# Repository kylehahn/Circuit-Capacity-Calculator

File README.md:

# Circuit Capacity Calculator

Native Qt 6 + C++20 desktop calculator and 3D editor for capacitance of
layered PCB topologies, solved via BEM. The original browser prototype
(`sensor3d_editor.html`) is kept separately as a behavioural reference.

## Quick start (any platform)

```
git clone <repo-url> circuit-capacity-calculator
cd circuit-capacity-calculator
# 1. Bootstrap vcpkg (one-time per machine, idempotent):
tools/bootstrap.sh         # macOS / Linux
tools\bootstrap.ps1        # Windows (PowerShell)

# 2. Configure + build:
cmake --preset linux-release        # macos-release / windows-release
cmake --build --preset linux-release -j
ctest --preset linux-release

# 3. Run:
./build/linux-release/circuit_capacity_calculator
```

> First configure compiles Qt from source via vcpkg — **30–60 minutes**. Every
> subsequent configure on the same machine is seconds, and CI/cache covers
> other machines.

## Prerequisites

| Platform | Compiler | Other |
|----------|----------|-------|
| Windows  | Visual Studio 2022 (MSVC + "C++ CMake tools for Windows") | Git, PowerShell 7 |
| macOS    | Xcode 15+ command-line tools                    | Homebrew, `brew install cmake ninja pkg-config` |
| Linux    | GCC 12+ or Clang 15+                            | `sudo apt install build-essential cmake ninja-build git pkg-config libgl1-mesa-dev libxkbcommon-dev libxcb*-dev libxkbcommon-x11-dev` (full list in `.github/workflows/build.yml`) |

CMake **3.25** or newer. Ninja generator (faster than Visual Studio's MSBuild
generator). On Windows, Ninja and MSVC ship inside Visual Studio's
**Developer PowerShell** — the build commands below must be run from that
shell, not regular PowerShell:

> Start menu → search "**Developer PowerShell for VS 2022**" → run from there.
> Or open the project folder in Visual Studio and use its built-in terminal.

## Multi-machine workflow

This project is set up to move cleanly between machines:

- vcpkg is cloned into `external/vcpkg/` and pinned to a baseline. Both are
  managed by `tools/bootstrap.*` and never committed.
- CMake presets reference the bundled vcpkg, so no environment variables are
  needed.
- A pull → configure → build cycle on a new machine is the same three commands
  as above.

### Build cache (recommended)

Install **sccache** so re-builds across machines / sessions are fast:

```
# macOS
brew install sccache
# Windows
scoop install sccache         # or  winget install sccache
# Ubuntu
sudo apt install sccache
```

`CMakePresets.json` already wires `CMAKE_C{,XX}_COMPILER_LAUNCHER=sccache`, so
once it is on `PATH` it is used automatically. To share the cache across
machines, set `SCCACHE_BUCKET=<your-s3-bucket>` (and credentials) before
running configure — sccache will pull pre-built objects on the second
machine.

## Layout

```
circuit-capacity-calculator/
├── CLAUDE.md                project context for the AI dev assistant
├── README.md                this file
├── CMakeLists.txt           top-level build
├── CMakePresets.json        per-platform presets (Win/Mac/Linux × Debug/Release)
├── vcpkg.json               manifest: Qt6, Eigen, tinygltf, nlohmann_json, Catch2
├── .clang-format            C++ formatting (Google base, 110 cols)
├── .editorconfig            editor-agnostic basics
├── .gitignore / .gitattributes
├── src/                     application source
│   ├── CMakeLists.txt
│   └── main.cpp             scaffold entry point — replace with real UI
├── tests/                   Catch2 v3 tests, mirror src/
│   ├── CMakeLists.txt
│   └── test_smoke.cpp
├── tools/                   dev scripts (bootstrap, formatting, …)
│   ├── bootstrap.sh
│   └── bootstrap.ps1
├── .github/workflows/       CI matrix: Windows / macOS / Linux × Release
│   └── build.yml
└── external/                vcpkg lives here after bootstrap (gitignored)
```

## A note on paths with spaces

If your local clone path contains spaces, CMake and vcpkg can occasionally
misbehave. The safe move is to clone this repo into a path **without spaces**,
e.g. `C:\dev\circuit-capacity-calculator` or `~/code/circuit-capacity-calculator`.
The scaffold itself is portable — just `git clone` to the new path on the
new machine.

## License

TBD — add `LICENSE` in the repo root before publishing.

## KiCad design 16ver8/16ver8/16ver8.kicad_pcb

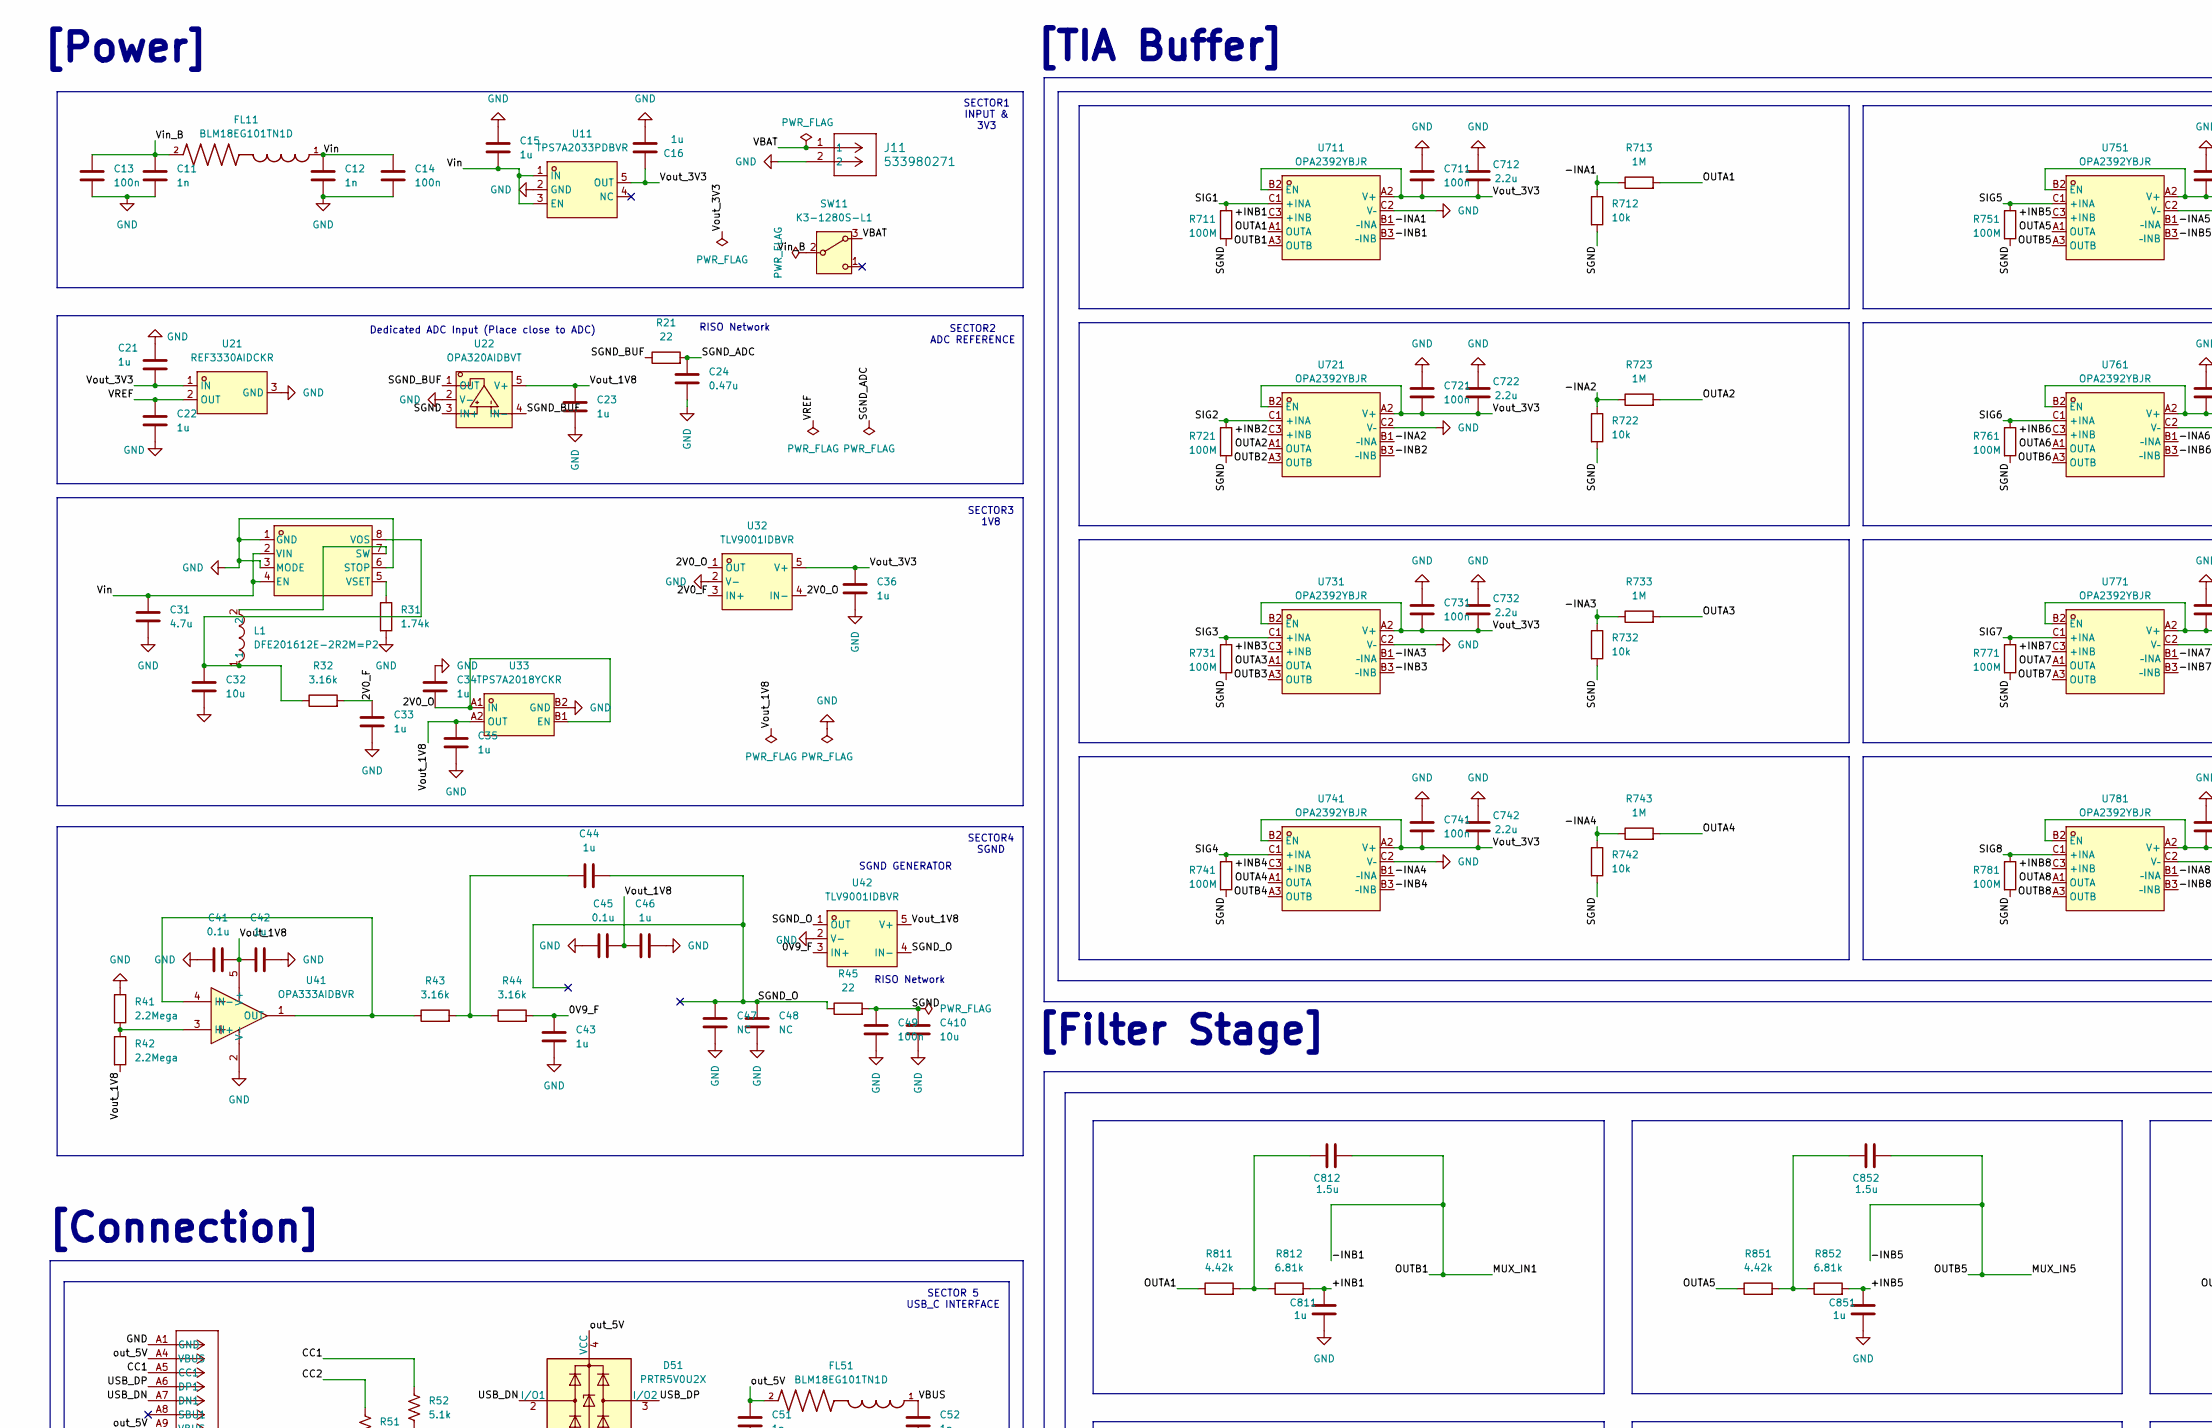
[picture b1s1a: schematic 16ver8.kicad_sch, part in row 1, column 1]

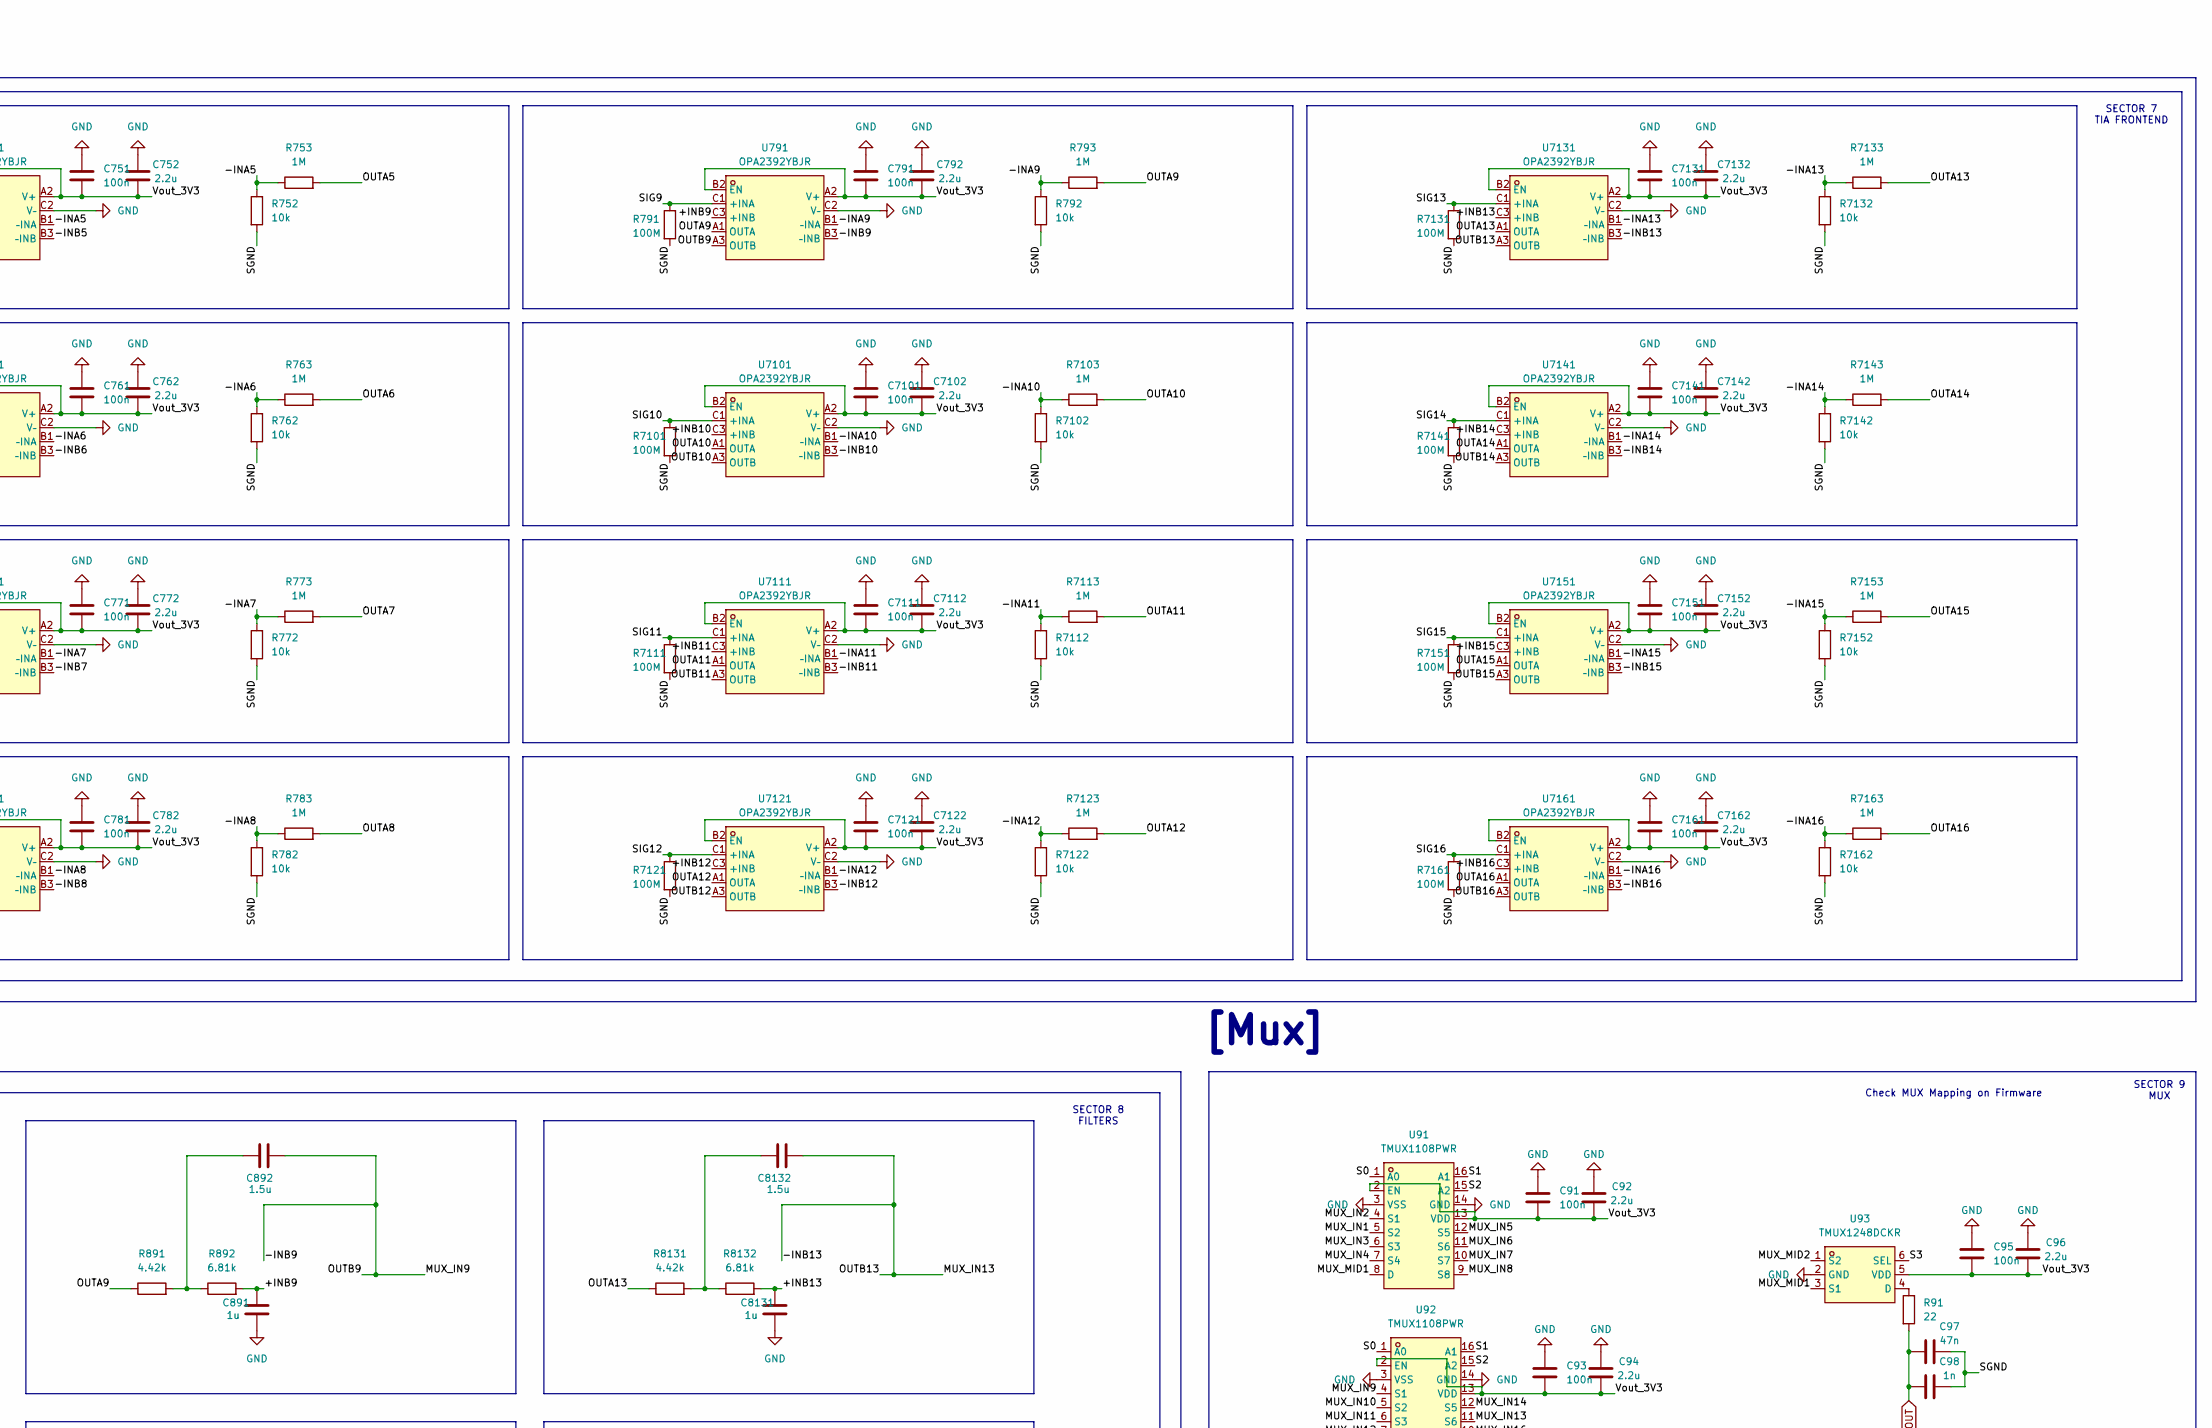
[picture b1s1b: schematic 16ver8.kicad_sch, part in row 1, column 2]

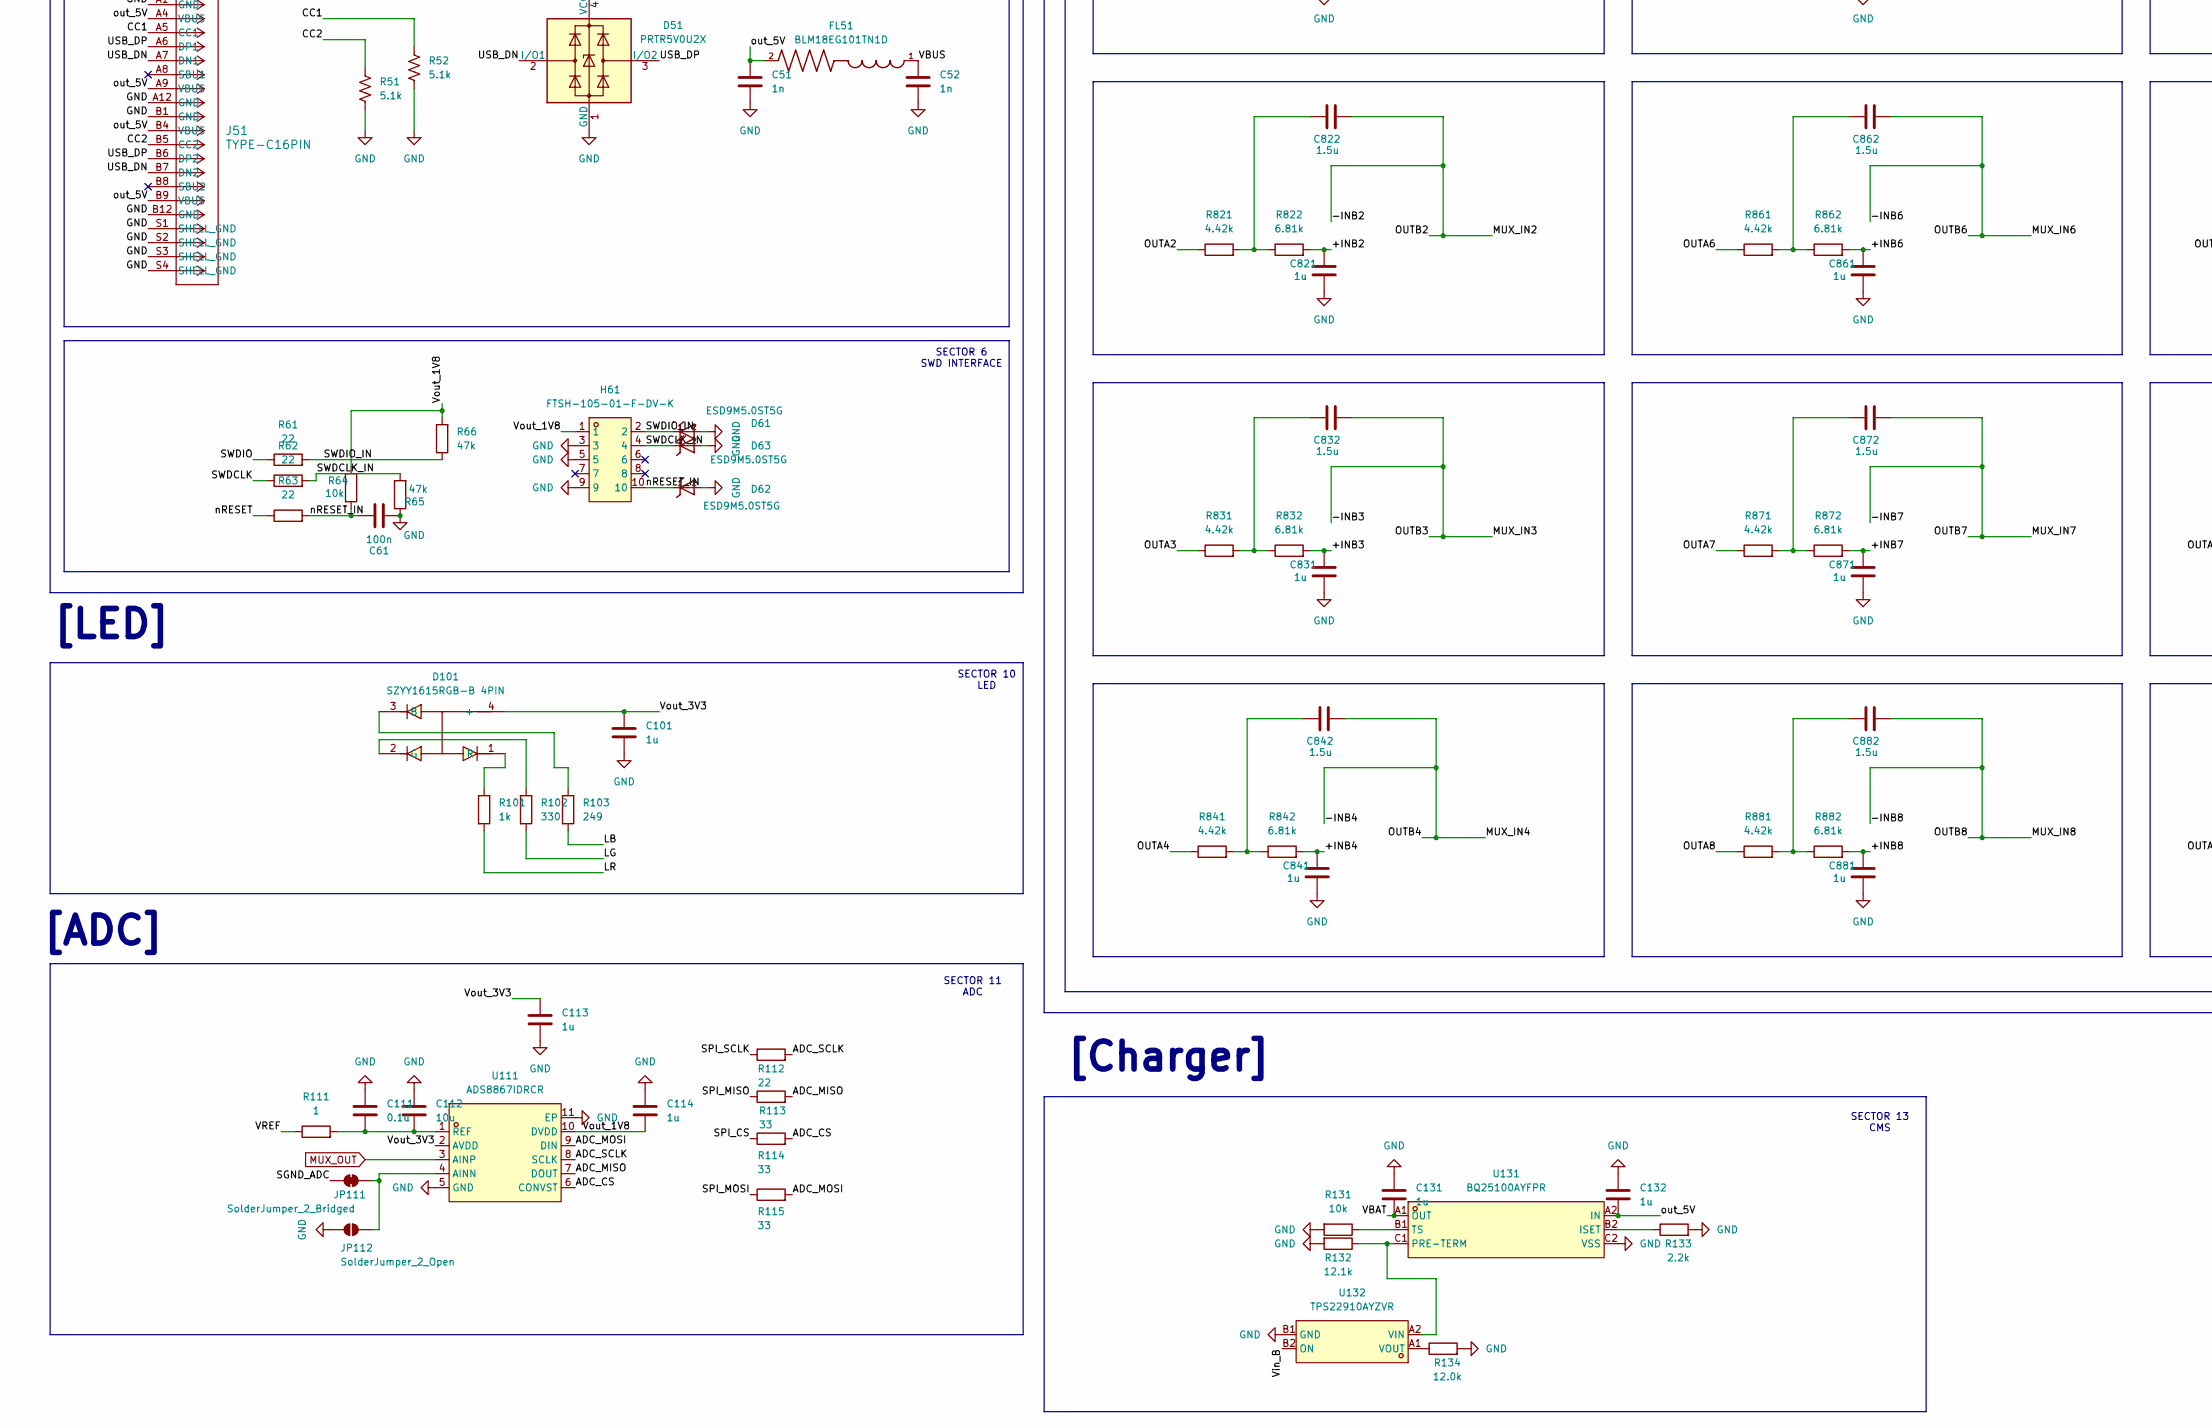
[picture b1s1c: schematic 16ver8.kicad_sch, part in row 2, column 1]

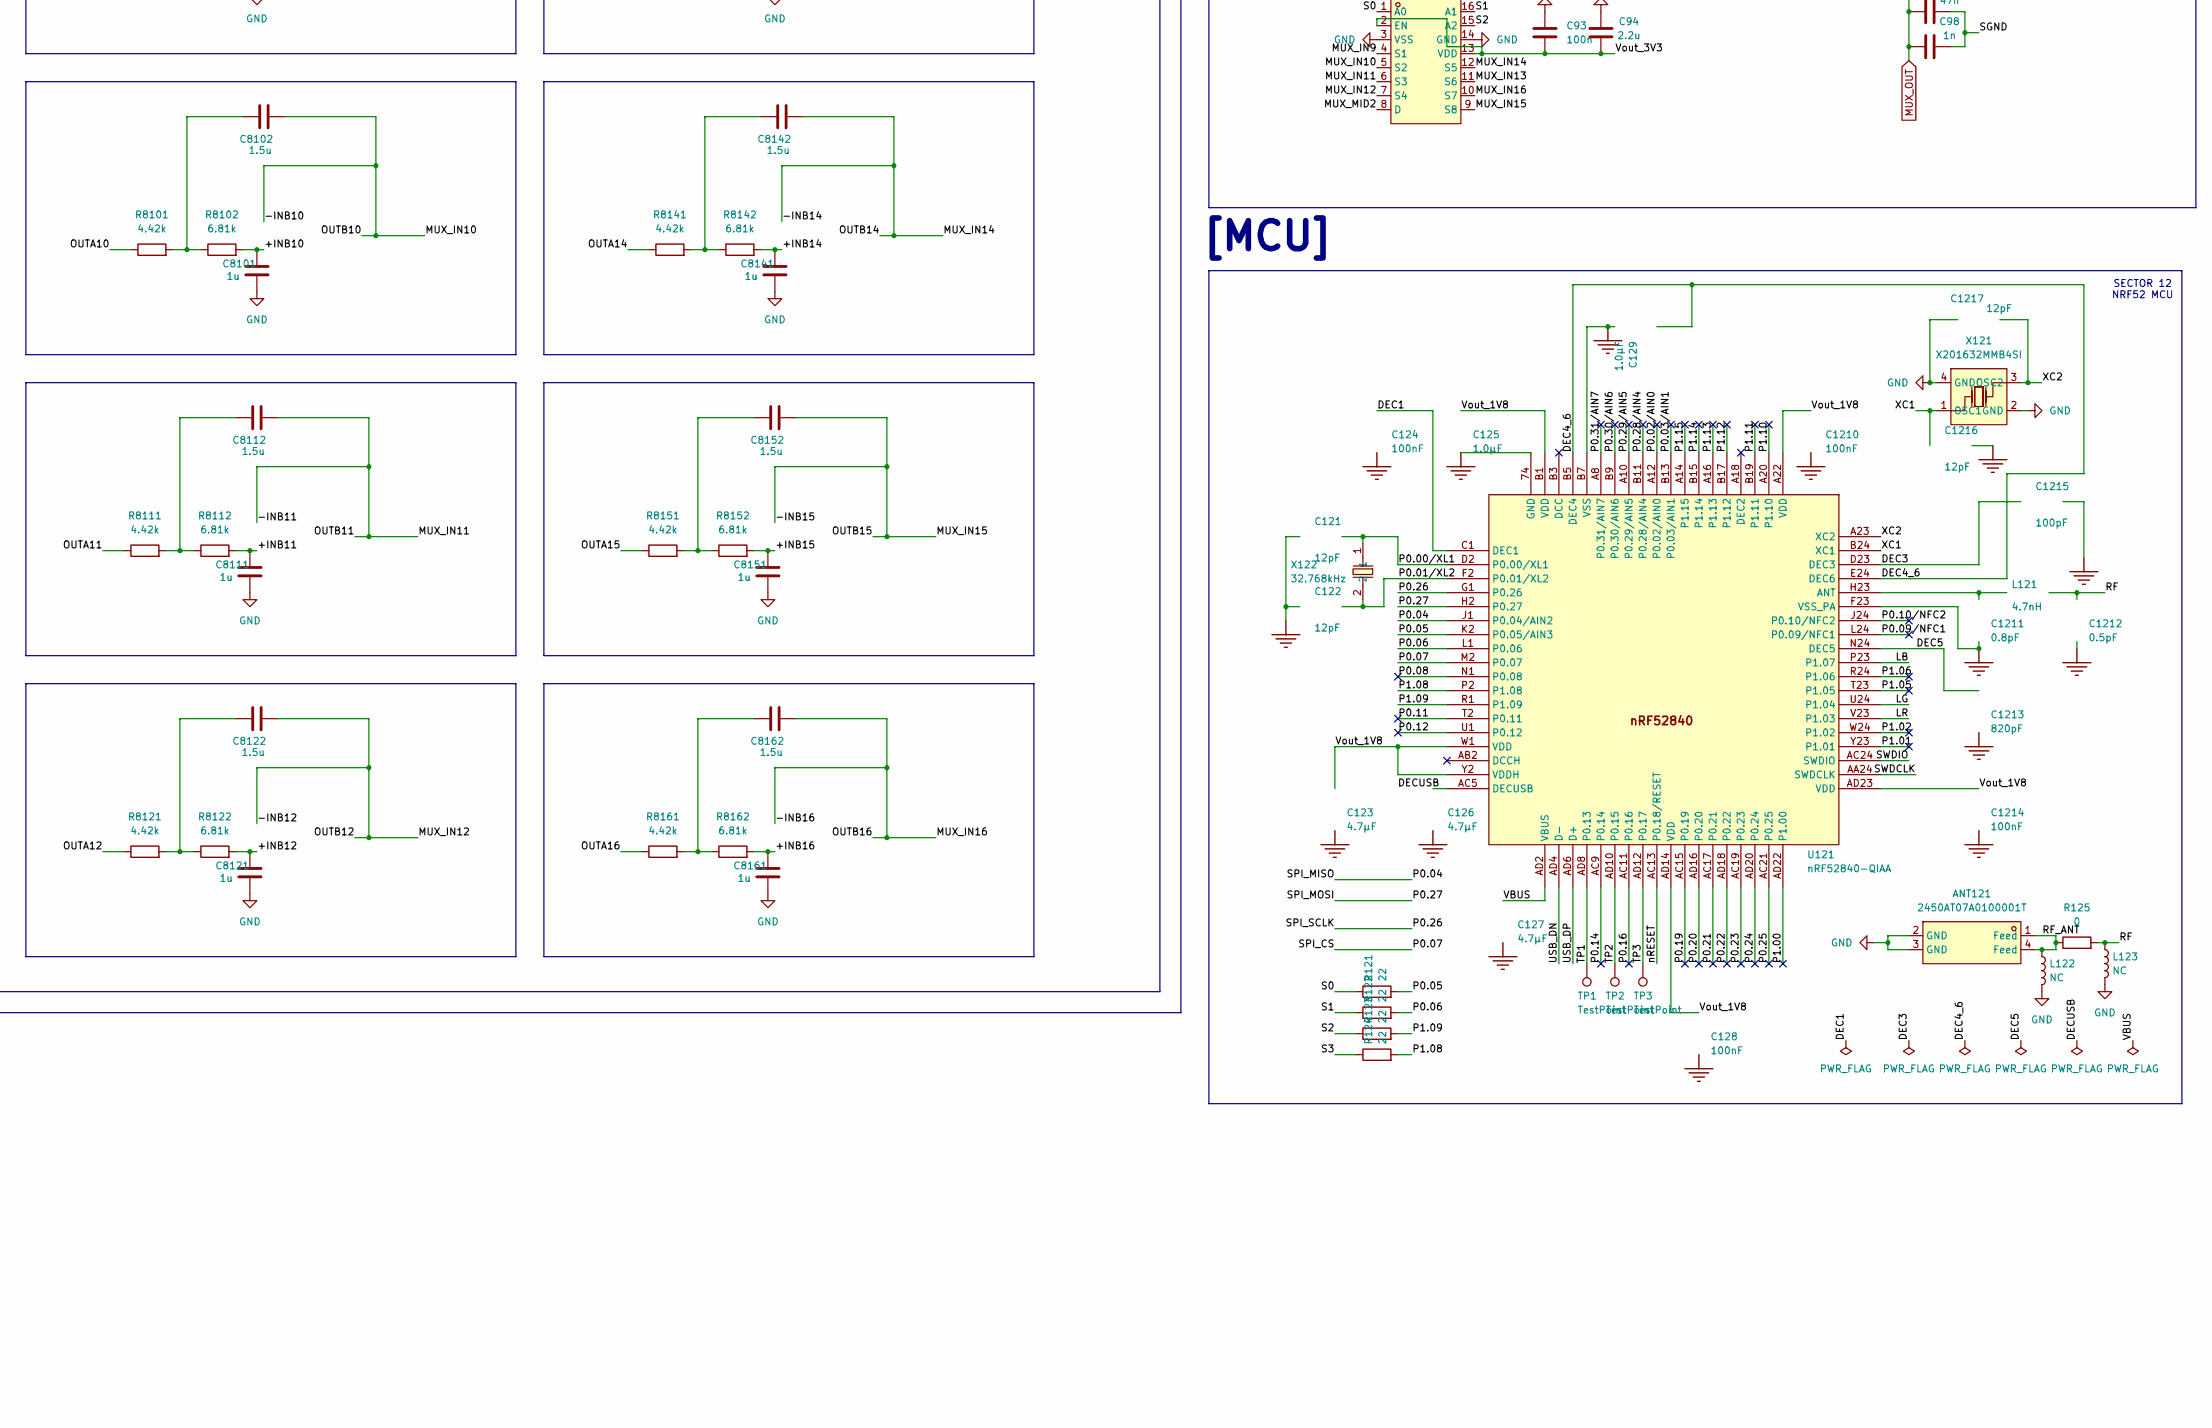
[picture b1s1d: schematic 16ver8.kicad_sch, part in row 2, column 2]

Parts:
ANT121: 2450AT07A0100001T; ANT-SMD_4P-L1.0-W0.5_2450AT07A0100001T; LCSC Part C17531353
C11, C12, C98: 1n; C_0402_1005Metric
C13, C14, C49, C61, C91, C93, C95, C711, C721, C731, C741, C751, C761, C771, C781, C791, C7101, C7111, C7121, C7131, C7141, C7151, C7161: 100n; C_0402_1005Metric
C15, C16, C21, C22, C23, C33, C34, C35, C36, C42, C46, C114, C811, C821, C831, C841, C851, C861, C871, C881, C891, C8101, C8111, C8121, C8131, C8141, C8151, C8161: 1u; C_0603_1608Metric
C24: 0.47u; C_0603_1608Metric
C31: 4.7u; C_0603_1608Metric
C32, C112, C410: 10u; C_0603_1608Metric
C41, C45: 0.1u; C_0402_1005Metric
C43, C44, C101, C113, C131, C132: 1u; C_0402_1005Metric
C47: NC; C_0402_1005Metric
C48: NC; C_0603_1608Metric
C51, C52: 1n; C_0603_1608Metric
C92, C94, C96, C712, C722, C732, C742, C752, C762, C772, C782, C792, C7102, C7112, C7122, C7132, C7142, C7152, C7162: 2.2u; C_0603_1608Metric
C97: 47n; C_0402_1005Metric
C111: 0.1u; C_0603_1608Metric
C121, C122, C1216, C1217: 12pF; CAPC1005X04L; PART NUMBER C0402-12p
C123, C126: 4.7µF; CAPC1608X06L; PART NUMBER C0603-4µ7-6.3V-X7R
C124, C128, C1210, C1214: 100nF; CAPC1005X04L; PART NUMBER C0402-100n
C125, C129: 1.0µF; CAPC1608X06L; PART NUMBER C0603-1µ0
C127: 4.7µF; CAPC1608X06L; PART NUMBER C0603-4µ7-10V-X7S
C812, C822, C832, C842, C852, C862, C872, C882, C892, C8102, C8112, C8122, C8132, C8142, C8152, C8162: 1.5u; C_0603_1608Metric
C1211: 0.8pF; CAPC1005X04L; PART NUMBER C0402-0.8p
C1212: 0.5pF; CAPC1005X04L; PART NUMBER C0402-0.5p
C1213: 820pF; CAPC1005X04L; PART NUMBER C0402-820p
C1215: 100pF; CAPC1005X04L; PART NUMBER C0402-100p
D51: PRTR5V0U2X; SOT-143
D61, D62, D63: ESD9M5.0ST5G; SODFL1060X40N
D101: SZYY1615RGB-B 4PIN; LED-SMD_4P-L1.6-W1.5-TR-1; LCSC Part C3029071
FL11, FL51: BLM18EG101TN1D; BEADC1608X65N
H61: FTSH-105-01-F-DV-K; HDR-SMD_FTSH-105-01-F-DV-K; LCSC Part C5382952
J11: 533980271; CONN02_533980271_MOL
J51: TYPE-C16PIN; TYPE-C-SMD_SBC-160S1A-20-S412
JP111: SolderJumper_2_Bridged; SolderJumper-2_P1.3mm_Bridged2Bar_Pad1.0x1.5mm
JP112: SolderJumper_2_Open; SolderJumper-2_P1.3mm_Open_Pad1.0x1.5mm
L1: DFE201612E-2R2M=P2; L0806; LCSC Part C337893
L121: 4.7nH; INDC1005X04L; PART NUMBER L0402-4n7
L122, L123: NC; L_0402_1005Metric
R21, R45, R61, R62, R63, R91, R112, R121, R122, R123, R124: 22; R_0402_1005Metric
R31: 1.74k; R_0402_1005Metric
R32, R43, R44: 3.16k; R_0402_1005Metric
R41, R42: 2.2Mega; R_0402_1005Metric
R51, R52: 5.1k; R_0402_1005Metric
R64, R131, R712, R722, R732, R742, R752, R762, R772, R782, R792, R7102, R7112, R7122, R7132, R7142, R7152, R7162: 10k; R_0402_1005Metric
R65, R66: 47k; R_0402_1005Metric
R101: 1k; R_0402_1005Metric
R102: 330; R_0402_1005Metric
R103: 249; R_0402_1005Metric
R111: 1; R_0402_1005Metric
R113, R114, R115: 33; R_0402_1005Metric
R125: 0; R_0402_1005Metric
R132: 12.1k; R_0402_1005Metric
R133: 2.2k; R_0402_1005Metric
R134: 12.0k; R_0402_1005Metric
R711, R721, R731, R741, R751, R761, R771, R781, R791, R7101, R7111, R7121, R7131, R7141, R7151, R7161: 100M; R_0805_2012Metric
R713, R723, R733, R743, R753, R763, R773, R783, R793, R7103, R7113, R7123, R7133, R7143, R7153, R7163: 1M; R_0603_1608Metric
R811, R821, R831, R841, R851, R861, R871, R881, R891, R8101, R8111, R8121, R8131, R8141, R8151, R8161: 4.42k; R_0402_1005Metric
R812, R822, R832, R842, R852, R862, R872, R882, R892, R8102, R8112, R8122, R8132, R8142, R8152, R8162: 6.81k; R_0402_1005Metric
SW11: K3-1280S-L1; SW_Nidec_CAS-120A1
TP1, TP2, TP3: TestPoint; TestPoint_Pad_1.0x1.0mm
U11: TPS7A2033PDBVR; SOT-23-5_L2.9-W1.6-P0.95-LS2.8-BR; LCSC Part C2862740
U21: REF3330AIDCKR; SC-70-3_L2.0-W1.3-P0.65-LS2.1-BL; LCSC Part C2157700
U22: OPA320AIDBVT; SOT-23-5_L2.9-W1.6-P0.95-LS2.8-BL; LCSC Part C206063
U31: TPS62840DLCR; VSON-8_L2.0-W1.5-P0.50-BL
U32, U42: TLV9001IDBVR; SOT-23-5_L3.0-W1.7-P0.95-LS2.8-BR; LCSC Part C398363
U33: TPS7A2018YCKR; BGA-4_L0.6-W0.6-P0.35-R2-C2-TL_TPS7A2012PYCJR; LCSC Part C42038768
U41: OPA333AIDBVR; SOT-23-5_L3.0-W1.7-P0.95-LS2.8-BR; LCSC Part C30878
U91, U92: TMUX1108PWR; TSSOP-16_L5.0-W4.4-P0.65-LS6.4-BL; LCSC Part C1021800
U93: TMUX1248DCKR; SC-70-6_L2.0-W1.3-P0.65-LS2.2-BL; LCSC Part C3656915
U111: ADS8867IDRCR; WSON-10_L3.0-W3.0-P0.50-BL-EP; LCSC Part C545498
U121: nRF52840-QIAA; AQFN-73_L7.0-W7.0-P0.50-BL-EP4.8; PART NUMBER nRF52840-QIAA
U131: BQ25100AYFPR; DSBGA-6_L0.9-W1.6-R2-C3-P0.40-BL; LCSC Part C2871910
U132: TPS22910AYZVR; DSBGA-4_L0.9-W0.9-R2-C2-P0.50-BL; LCSC Part C205966
U711, U721, U731, U741, U751, U761, U771, U781, U791, U7101, U7111, U7121, U7131, U7141, U7151, U7161: OPA2392YBJR; DSBGA-9_L1.2-W1.2-R3-C3-P0.40-BL; LCSC Part C5946032
X121: X201632MMB4SI; CRYSTAL-SMD_4P-L2.0-W1.6-BL; LCSC Part C383840
X122: 32.768kHz; CRYSTAL-SMD_L2.0-W1.2; LCSC Part C32346

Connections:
/0V9_F: C43.1, R44.2, U42.3 (IN+)
/2V0_F: C33.1, R32.2, U32.3 (IN+)
/2V0_O: C34.2, U32.1 (OUT), U32.4 (IN-), U33.A1 (IN), U33.B1 (EN)
/+INB1: C811.1, R812.2, U711.C3 (+INB)
/+INB2: C821.1, R822.2, U721.C3 (+INB)
/+INB3: C831.1, R832.2, U731.C3 (+INB)
/+INB4: C841.1, R842.2, U741.C3 (+INB)
/+INB5: C851.1, R852.2, U751.C3 (+INB)
/+INB6: C861.1, R862.2, U761.C3 (+INB)
/+INB7: C871.1, R872.2, U771.C3 (+INB)
/+INB8: C881.1, R882.2, U781.C3 (+INB)
/+INB9: C891.1, R892.2, U791.C3 (+INB)
/+INB10: C8101.1, R8102.2, U7101.C3 (+INB)
/+INB11: C8111.1, R8112.2, U7111.C3 (+INB)
/+INB12: C8121.1, R8122.2, U7121.C3 (+INB)
/+INB13: C8131.1, R8132.2, U7131.C3 (+INB)
/+INB14: C8141.1, R8142.2, U7141.C3 (+INB)
/+INB15: C8151.1, R8152.2, U7151.C3 (+INB)
/+INB16: C8161.1, R8162.2, U7161.C3 (+INB)
/-INA1: R712.1, R713.1, U711.B1 (–INA)
/-INA2: R722.1, R723.1, U721.B1 (–INA)
/-INA3: R732.1, R733.1, U731.B1 (–INA)
/-INA4: R742.1, R743.1, U741.B1 (–INA)
/-INA5: R752.1, R753.1, U751.B1 (–INA)
/-INA6: R762.1, R763.1, U761.B1 (–INA)
/-INA7: R772.1, R773.1, U771.B1 (–INA)
/-INA8: R782.1, R783.1, U781.B1 (–INA)
/-INA9: R792.1, R793.1, U791.B1 (–INA)
/-INA10: R7102.1, R7103.1, U7101.B1 (–INA)
/-INA11: R7112.1, R7113.1, U7111.B1 (–INA)
/-INA12: R7122.1, R7123.1, U7121.B1 (–INA)
/-INA13: R7132.1, R7133.1, U7131.B1 (–INA)
/-INA14: R7142.1, R7143.1, U7141.B1 (–INA)
/-INA15: R7152.1, R7153.1, U7151.B1 (–INA)
/-INA16: R7162.1, R7163.1, U7161.B1 (–INA)
/-INB1: C812.2, U91.5 (S2), U711.A3 (OUTB), U711.B3 (–INB)
/-INB2: C822.2, U91.4 (S1), U721.A3 (OUTB), U721.B3 (–INB)
/-INB3: C832.2, U91.6 (S3), U731.A3 (OUTB), U731.B3 (–INB)
/-INB4: C842.2, U91.7 (S4), U741.A3 (OUTB), U741.B3 (–INB)
/-INB5: C852.2, U91.12 (S5), U751.A3 (OUTB), U751.B3 (–INB)
/-INB6: C862.2, U91.11 (S6), U761.A3 (OUTB), U761.B3 (–INB)
/-INB7: C872.2, U91.10 (S7), U771.A3 (OUTB), U771.B3 (–INB)
/-INB8: C882.2, U91.9 (S8), U781.A3 (OUTB), U781.B3 (–INB)
/-INB9: C892.2, U92.4 (S1), U791.A3 (OUTB), U791.B3 (–INB)
/-INB10: C8102.2, U92.5 (S2), U7101.A3 (OUTB), U7101.B3 (–INB)
/-INB11: C8112.2, U92.6 (S3), U7111.A3 (OUTB), U7111.B3 (–INB)
/-INB12: C8122.2, U92.7 (S4), U7121.A3 (OUTB), U7121.B3 (–INB)
/-INB13: C8132.2, U92.11 (S6), U7131.A3 (OUTB), U7131.B3 (–INB)
/-INB14: C8142.2, U92.12 (S5), U7141.A3 (OUTB), U7141.B3 (–INB)
/-INB15: C8152.2, U92.9 (S8), U7151.A3 (OUTB), U7151.B3 (–INB)
/-INB16: C8162.2, U92.10 (S7), U7161.A3 (OUTB), U7161.B3 (–INB)
/ADC_CS: R114.2, U111.6 (CONVST)
/ADC_MISO: R113.2, U111.7 (DOUT)
/ADC_MOSI: R115.2, U111.9 (DIN)
/ADC_SCLK: R112.2, U111.8 (SCLK)
/CC1: J51.A5 (CC1), R52.1
/CC2: J51.B5 (CC2), R51.1
/DEC1: C124.1, U121.C1 (DEC1)
/DEC3: C1215.1, U121.D23 (DEC3)
/DEC4_6: C129.2, U121.B5 (DEC4), U121.E24 (DEC6)
/DEC5: C1213.1, U121.N24 (DEC5)
/DECUSB: C126.1, U121.AC5 (DECUSB)
/LB: R103.2, U121.P23 (P1.07)
/LG: R102.2, U121.U24 (P1.04)
/LR: R101.2, U121.V23 (P1.03)
/MUX_MID1: U91.8 (D), U93.3 (S1)
/MUX_MID2: U92.8 (D), U93.1 (S2)
/OUTA1: R713.2, R811.1, U711.A1 (OUTA)
/OUTA2: R723.2, R821.1, U721.A1 (OUTA)
/OUTA3: R733.2, R831.1, U731.A1 (OUTA)
/OUTA4: R743.2, R841.1, U741.A1 (OUTA)
/OUTA5: R753.2, R851.1, U751.A1 (OUTA)
/OUTA6: R763.2, R861.1, U761.A1 (OUTA)
/OUTA7: R773.2, R871.1, U771.A1 (OUTA)
/OUTA8: R783.2, R881.1, U781.A1 (OUTA)
/OUTA9: R793.2, R891.1, U791.A1 (OUTA)
/OUTA10: R7103.2, R8101.1, U7101.A1 (OUTA)
/OUTA11: R7113.2, R8111.1, U7111.A1 (OUTA)
/OUTA12: R7123.2, R8121.1, U7121.A1 (OUTA)
/OUTA13: R7133.2, R8131.1, U7131.A1 (OUTA)
/OUTA14: R7143.2, R8141.1, U7141.A1 (OUTA)
/OUTA15: R7153.2, R8151.1, U7151.A1 (OUTA)
/OUTA16: R7163.2, R8161.1, U7161.A1 (OUTA)
/P0.00/XL1: C121.1, U121.D2 (P0.00/XL1), X122.1
/P0.01/XL2: C122.1, U121.F2 (P0.01/XL2), X122.2
/P0.02/AIN0: U121.A12 (P0.02/AIN0)
/P0.03/AIN1: U121.B13 (P0.03/AIN1)
/P0.04: R113.1, U121.J1 (P0.04/AIN2)
/P0.05: R121.2, U121.K2 (P0.05/AIN3)
/P0.06: R122.2, U121.L1 (P0.06)
/P0.07: R114.1, U121.M2 (P0.07)
/P0.08: U121.N1 (P0.08)
/P0.09/NFC1: U121.L24 (P0.09/NFC1)
/P0.10/NFC2: U121.J24 (P0.10/NFC2)
/P0.11: U121.T2 (P0.11)
/P0.12: U121.U1 (P0.12)
/P0.14: U121.AC9 (P0.14)
/P0.16: U121.AC11 (P0.16)
/P0.19: U121.AC15 (P0.19)
/P0.20: U121.AD16 (P0.20)
/P0.21: U121.AC17 (P0.21)
/P0.22: U121.AD18 (P0.22)
/P0.23: U121.AC19 (P0.23)
/P0.24: U121.AD20 (P0.24)
/P0.25: U121.AC21 (P0.25)
/P0.26: R112.1, U121.G1 (P0.26)
/P0.27: R115.1, U121.H2 (P0.27)
/P0.28/AIN4: U121.B11 (P0.28/AIN4)
/P0.29/AIN5: U121.A10 (P0.29/AIN5)
/P0.30/AIN6: U121.B9 (P0.30/AIN6)
/P0.31/AIN7: U121.A8 (P0.31/AIN7)
/P1.00: U121.AD22 (P1.00)
/P1.01: U121.Y23 (P1.01)
/P1.02: U121.W24 (P1.02)
/P1.05: U121.T23 (P1.05)
/P1.06: U121.R24 (P1.06)
/P1.08: R124.2, U121.P2 (P1.08)
/P1.09: R123.2, U121.R1 (P1.09)
/P1.10: U121.A20 (P1.10)
/P1.11: U121.B19 (P1.11)
/P1.12: U121.B17 (P1.12)
/P1.13: U121.A16 (P1.13)
/P1.14: U121.B15 (P1.14)
/P1.15: U121.A14 (P1.15)
/RF: C1212.2, L121.2, L123.1, R125.2
/RF_ANT: ANT121.1 (Feed), ANT121.4 (Feed), L122.1, R125.1
/S0: R121.1, U91.1 (A0), U92.1 (A0)
/S1: R122.1, U91.16 (A1), U92.16 (A1)
/S2: R123.1, U91.15 (A2), U92.15 (A2)
/S3: R124.1, U93.6 (SEL)
/SGND: C49.2, C97.2, C98.2, C410.1, R45.2, R711.2, R712.2, R721.2, R722.2, R731.2, R732.2, R741.2, R742.2, R751.2, R752.2, R761.2, R762.2, R771.2, R772.2, R781.2, R782.2, R791.2, R792.2, R7101.2, R7102.2, R7111.2, R7112.2, R7121.2, R7122.2, R7131.2, R7132.2, R7141.2, R7142.2, R7151.2, R7152.2, R7161.2, R7162.2, U22.3 (IN+)
/SGND_ADC: C24.1, JP111.2 (B), R21.2
/SGND_BUF: R21.1, U22.1 (OUT), U22.4 (IN-)
/SGND_O: C44.2, C47.2, C48.1, R45.1, U42.1 (OUT), U42.4 (IN-)
/SIG1: R711.1, U711.C1 (+INA)
/SIG2: R721.1, U721.C1 (+INA)
/SIG3: R731.1, U731.C1 (+INA)
/SIG4: R741.1, U741.C1 (+INA)
/SIG5: R751.1, U751.C1 (+INA)
/SIG6: R761.1, U761.C1 (+INA)
/SIG7: R771.1, U771.C1 (+INA)
/SIG8: R781.1, U781.C1 (+INA)
/SIG9: R791.1, U791.C1 (+INA)
/SIG10: R7101.1, U7101.C1 (+INA)
/SIG11: R7111.1, U7111.C1 (+INA)
/SIG12: R7121.1, U7121.C1 (+INA)
/SIG13: R7131.1, U7131.C1 (+INA)
/SIG14: R7141.1, U7141.C1 (+INA)
/SIG15: R7151.1, U7151.C1 (+INA)
/SIG16: R7161.1, U7161.C1 (+INA)
/SWDCLK: R62.1, U121.AA24 (SWDCLK)
/SWDCLK_IN: D63.1, H61.4, R62.2, R65.2
/SWDIO: R61.1, U121.AC24 (SWDIO)
/SWDIO_IN: D61.1, H61.2, R61.2, R66.1
/TP1: TP1.1, U121.AD8 (P0.13)
/TP2: TP2.1, U121.AD10 (P0.15)
/TP3: TP3.1, U121.AD12 (P0.17)
/USB_DN: D51.2 (I/O1), J51.A7 (DN1), J51.B7 (DN2), U121.AD4 (D-)
/USB_DP: D51.3 (I/O2), J51.A6 (DP1), J51.B6 (DP2), U121.AD6 (D+)
/VBAT: C131.1, J11.1, SW11.3 (A), U131.A1 (OUT)
/VBUS: C52.1, C127.1, FL51.1, U121.AD2 (VBUS)
/VREF: C22.1, R111.1, U21.2 (OUT)
/Vin: C12.1, C14.1, C15.2, C31.1, FL11.1, U11.1 (IN), U11.3 (EN), U31.2 (VIN), U31.4 (EN)
/Vin_B: C11.1, C13.1, FL11.2, SW11.2 (B), U132.B2 (ON)
/Vout_1V8: C23.1, C35.1, C41.2, C42.1, C45.2, C46.1, C114.2, C123.1, C125.1, C128.1, C1210.1, C1214.1, H61.1, R42.2, R64.1, R66.2, U22.5 (V+), U33.A2 (OUT), U41.5 (V+), U42.5 (V+), U111.10 (DVDD), U121.A22 (VDD), U121.AD14 (VDD), U121.AD23 (VDD), U121.B1 (VDD), U121.W1 (VDD), U121.Y2 (VDDH)
/Vout_3V3: C16.1, C21.1, C36.1, C91.1, C92.1, C93.1, C94.1, C95.1, C96.1, C101.1, C113.1, C711.1, C712.1, C721.1, C722.1, C731.1, C732.1, C741.1, C742.1, C751.1, C752.1, C761.1, C762.1, C771.1, C772.1, C781.1, C782.1, C791.1, C792.1, C7101.1, C7102.1, C7111.1, C7112.1, C7121.1, C7122.1, C7131.1, C7132.1, C7141.1, C7142.1, C7151.1, C7152.1, C7161.1, C7162.1, D101.4 (+), U11.5 (OUT), U21.1 (IN), U32.5 (V+), U91.2 (EN), U91.13 (VDD), U92.2 (EN), U92.13 (VDD), U93.5 (VDD), U111.2 (AVDD), U711.A2 (V+), U711.B2 (EN), U721.A2 (V+), U721.B2 (EN), U731.A2 (V+), U731.B2 (EN), U741.A2 (V+), U741.B2 (EN), U751.A2 (V+), U751.B2 (EN), U761.A2 (V+), U761.B2 (EN), U771.A2 (V+), U771.B2 (EN), U781.A2 (V+), U781.B2 (EN), U791.A2 (V+), U791.B2 (EN), U7101.A2 (V+), U7101.B2 (EN), U7111.A2 (V+), U7111.B2 (EN), U7121.A2 (V+), U7121.B2 (EN), U7131.A2 (V+), U7131.B2 (EN), U7141.A2 (V+), U7141.B2 (EN), U7151.A2 (V+), U7151.B2 (EN), U7161.A2 (V+), U7161.B2 (EN)
/XC1: C1216.1, U121.B24 (XC1), X121.1 (OSC1)
/XC2: C1217.1, U121.A23 (XC2), X121.3 (OSC2)
/nRESET: R63.1, U121.AC13 (P0.18/RESET)
/nRESET_IN: C61.2, D62.1, H61.10, R63.2, R64.2
/out_5V: C51.1, C132.1, D51.4 (VCC), FL51.2, J51.A4 (VBUS), J51.A9 (VBUS), J51.B4 (VBUS), J51.B9 (VBUS), U131.A2 (IN)
GND: ANT121.2 (GND), ANT121.3 (GND), C11.2, C12.2, C13.2, C14.2, C15.1, C16.2, C21.2, C22.2, C23.2, C24.2, C31.2, C32.2, C33.2, C34.1, C35.2, C36.2, C41.1, C42.2, C43.2, C45.1, C46.2, C47.1, C48.2, C49.1, C51.2, C52.2, C61.1, C91.2, C92.2, C93.2, C94.2, C95.2, C96.2, C101.2, C111.1, C112.1, C113.2, C114.1, C121.2, C122.2, C123.2, C124.2, C125.2, C126.2, C127.2, C128.2, C129.1, C131.2, C132.2, C410.2, C711.2, C712.2, C721.2, C722.2, C731.2, C732.2, C741.2, C742.2, C751.2, C752.2, C761.2, C762.2, C771.2, C772.2, C781.2, C782.2, C791.2, C792.2, C811.2, C821.2, C831.2, C841.2, C851.2, C861.2, C871.2, C881.2, C891.2, C1210.2, C1211.1, C1212.1, C1213.2, C1214.2, C1215.2, C1216.2, C1217.2, C7101.2, C7102.2, C7111.2, C7112.2, C7121.2, C7122.2, C7131.2, C7132.2, C7141.2, C7142.2, C7151.2, C7152.2, C7161.2, C7162.2, C8101.2, C8111.2, C8121.2, C8131.2, C8141.2, C8151.2, C8161.2, D51.1 (GND), D61.2, D62.2, D63.2, H61.3, H61.5, H61.9, J11.2, J51.A1 (GND), J51.A12 (GND), J51.B1 (GND), J51.B12 (GND), J51.S1 (SHELL_GND), J51.S2 (SHELL_GND), J51.S3 (SHELL_GND), J51.S4 (SHELL_GND), JP112.1 (A), L122.2, L123.2, R31.2, R41.1, R51.2, R52.2, R65.1, R131.2, R132.2, R133.2, R134.2, U11.2 (GND), U21.3 (GND), U22.2 (V-), U31.1 (GND), U31.3 (MODE), U31.6 (STOP), U32.2 (V-), U33.B2 (GND), U41.2 (V-), U42.2 (V-), U91.3 (VSS), U91.14 (GND), U92.3 (VSS), U92.14 (GND), U93.2 (GND), U111.5 (GND), U111.11 (EP), U121.74 (GND), U121.B7 (VSS), U121.F23 (VSS_PA), U131.C2 (VSS), U132.B1 (GND), U711.C2 (V–), U721.C2 (V–), U731.C2 (V–), U741.C2 (V–), U751.C2 (V–), U761.C2 (V–), U771.C2 (V–), U781.C2 (V–), U791.C2 (V–), U7101.C2 (V–), U7111.C2 (V–), U7121.C2 (V–), U7131.C2 (V–), U7141.C2 (V–), U7151.C2 (V–), U7161.C2 (V–), X121.2 (GND), X121.4 (GND)
MUX_OUT: C97.1, C98.1, R91.2, U111.3 (AINP)
unnamed: C44.1, R43.2, R44.1
unnamed: C812.1, R811.2, R812.1
unnamed: C822.1, R821.2, R822.1
unnamed: C832.1, R831.2, R832.1
unnamed: C842.1, R841.2, R842.1
unnamed: C852.1, R851.2, R852.1
unnamed: C862.1, R861.2, R862.1
unnamed: C872.1, R871.2, R872.1
unnamed: C882.1, R881.2, R882.1
unnamed: C892.1, R891.2, R892.1
unnamed: C8102.1, R8101.2, R8102.1
unnamed: C8112.1, R8111.2, R8112.1
unnamed: C8122.1, R8121.2, R8122.1
unnamed: C8132.1, R8131.2, R8132.1
unnamed: C8142.1, R8141.2, R8142.1
unnamed: C8152.1, R8151.2, R8152.1
unnamed: C8162.1, R8161.2, R8162.1
unnamed: D101.3 (B), R103.1
unnamed: D101.2 (G), R102.1
unnamed: D101.1 (R), R101.1
unnamed: JP111.1 (A), JP112.2 (B), U111.4 (AINN)
unnamed: L1.2, U31.7 (SW)
unnamed: C32.1, L1.1, R32.1, U31.8 (VOS)
unnamed: R31.1, U31.5 (VSET)
unnamed: R41.2, R42.1, U41.3 (IN+)
unnamed: R43.1, U41.1 (OUT), U41.4 (IN-)
unnamed: R91.1, U93.4 (D)
unnamed: C111.2, C112.2, R111.2, U111.1 (REF)
unnamed: C1211.2, L121.1, U121.H23 (ANT)
unnamed: R133.1, U131.B2 (ISET)
unnamed: R132.1, U131.C1 (PRE-TERM), U132.A2 (VIN)
unnamed: R131.1, U131.B1 (TS)
unnamed: R134.1, U132.A1 (VOUT)

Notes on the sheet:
[TIA Buffer]
Dedicated ADC Input (Place close to ADC)
Check MUX Mapping on Firmware
[MCU]
SGND GENERATOR
SECTOR 8 FILTERS
SECTOR4 SGND
SECTOR1 INPUT & 3V3
SECTOR 5 USB_C INTERFACE
[Mux]
SECTOR2 ADC REFERENCE
SECTOR 11 ADC
[Power]
[ADC]
[Filter Stage]
SECTOR 12 NRF52 MCU
[Connection]
RISO Network
SECTOR 13 CMS
SECTOR 7 TIA FRONTEND
SECTOR 6 SWD INTERFACE
SECTOR 10 LED
[Charger]
SECTOR 9 MUX
SECTOR3 1V8
[LED]
